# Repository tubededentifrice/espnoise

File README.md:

# ESPNoise

ESPNoise is a privacy-first noise warning sign for shared workspaces. An ESP32
measures sound energy and lights the word **NOISE** only when the room stays
loud. Short sounds, such as a cough or a dropped object, do not start the
alarm by themselves.

The repository includes the production enclosure, hardware design, PlatformIO
firmware, and an optional iPhone settings app.

## Main features

- Sustained-noise detection with a rolling decision window
- Green, orange, and red warning levels
- Ten SK6812 RGB plus warm-white pixels behind a printed diffuser
- Optional passive buzzer with a hard power switch
- A 30-minute mute button
- No raw microphone recording or storage
- Wi-Fi off; Bluetooth Low Energy is used only for the optional app
- Firmware targets for a full-size ESP32 and a LOLIN32 Lite

## Production build

The production build uses a full-size ESP32 board and a separate, power-only
USB-C input. A regulated 5 V supply powers the controller and peripherals. The
ESP32 USB-C port stays inside the enclosure as a firmware-service port. No
battery is necessary.

| Item | Production specification |
| --- | --- |
| Controller | Full-size ESP32 development board with USB-C |
| Microphone | ICS-43434 digital I2S microphone on the carrier PCB |
| Display | 10 SK6812 RGB plus warm-white, 32-bit pixels |
| Data buffer | SN74AHCT125PWR, 3.3 V input to 5 V output |
| Sound | 5 V passive electromagnetic buzzer and MMBT3904 driver |
| Controls | Momentary mute button and maintained hard buzzer switch |
| Power | Regulated 5 V, 2 A minimum; 3 A recommended |
| Enclosure | 164 mm × 54 mm × 54.5 mm main case envelope |

See the [bill of materials](docs/bom.md) for the complete part specification.

## 3D-print files

The ready-to-print package and editable source are in
[`cad/production`](cad/production). Start with one of these files:

- [`espnoise.3mf`](cad/production/espnoise.3mf) contains four arranged plates
  and the saved Bambu Studio print profile.
- [`espnoise.f3d`](cad/production/espnoise.f3d) is the editable Autodesk Fusion
  design.
- The individual STL files support other slicers and printers.

The package contains the case, back, reflector, illuminated letters, optional
letter mould, mute-button cap, and buzzer-switch cap.

| Reflector and switch cap | Case, back, and button cap | Letters | Letter mould |
| :---: | :---: | :---: | :---: |
|  |  |  |  |

The saved profile uses a 0.4 mm nozzle, 0.2 mm layers, two wall loops, 15%
infill, and no supports. Check the profile for your printer and material before
you print. See the [enclosure guide](cad/README.md) for file dimensions,
materials, and assembly notes.

## Wiring

The production wiring uses one common ground. The LED supply does not pass
through the ESP32 board.

```mermaid
flowchart LR
  USB["External power-only USB-C<br>5 V"] --> SPLIT["5 V and GND split"]
  SPLIT --> ESP["ESP32<br>5V/VIN and GND"]
  SPLIT --> FUSE["0.5 A hold fuse"]
  FUSE --> RAIL["5 V peripheral rail"]

  ESP -->|"3V3, GND<br>GPIO26 SCK<br>GPIO25 WS<br>GPIO32 SD"| MIC["ICS-43434<br>L/R to GND"]
  ESP -->|"GPIO18"| AHCT["SN74AHCT125PWR<br>5 V supply"]
  AHCT -->|"330 ohm"| LED["10 × SK6812 RGBW<br>5 V at both ends"]
  RAIL --> AHCT
  RAIL --> LED

  ESP -->|"GPIO23 PWM<br>through 1 kohm"| Q1["MMBT3904 driver"]
  RAIL --> SW["Hard buzzer<br>power switch"]
  SW --> BUZ["Passive magnetic buzzer"]
  BUZ --> Q1

  BTN["Mute button<br>GPIO27 to GND"] --> ESP
```

| Function | ESP32 pin |
| --- | ---: |
| ICS-43434 clock | GPIO26 |
| ICS-43434 word select | GPIO25 |
| ICS-43434 data | GPIO32 |
| SK6812 data through SN74AHCT125PWR | GPIO18 |
| Buzzer PWM through 1 kohm and MMBT3904 | GPIO23 |
| Mute button to GND | GPIO27 |
| Optional battery-boost enable | GPIO13 |

Keep the buzzer switch in the buzzer 5 V wire. Software must not override this
switch. Keep the external two-wire USB-C input separate from the ESP32
firmware-service port. If the power input exposes CC1 and CC2, connect one
5.1 kohm pull-down from each CC pin to GND. Do not connect CC1 to CC2.

See the [complete wiring guide](docs/wiring.md) and the
[interactive prototype-board diagram](docs/prototype-board-wiring.html) before
assembly.

## How detection works

The default rule listens for one second in each ten-second period. It stores
only the maximum sound level from each observation. At least three of the last
six observations must cross a threshold before the alarm starts. Two quiet
checks clear an active alarm.

The default thresholds are in dBFS until you calibrate the unit against a sound
level meter. They are not certified dBA values. Detector values and thresholds
are in [`firmware/include/config.h`](firmware/include/config.h).

## Build guide

1. Check the [bill of materials](docs/bom.md).
2. Print and prepare the [production enclosure](cad/README.md).
3. Follow the [modular assembly stages](docs/modular-build.md).
4. Make the connections in the [wiring guide](docs/wiring.md).
5. Build and upload the [firmware](firmware/README.md).
6. Use the [test and adjustment procedure](docs/detection.md).
7. If necessary, install and configure the optional iPhone app as described in
   [the app and Bluetooth guide](docs/app-and-bluetooth.md).

## Safety and privacy

- Start a new or changed build at 25% LED brightness or less. The production
  USB profile uses its higher limit only after the documented power test.
- Disconnect external 5 V power before you connect the ESP32 service USB port.
- Do not connect a battery to the full-size ESP32 board.
- For the optional battery build, use one protected 3.7 V LiPo pack with the
  correct plug polarity. Do not use loose lithium cells.
- Do not cover the microphone acoustic hole.
- The firmware processes sound levels in memory and does not save raw audio.

## Repository map

```text
cad/                 Production 3D-print files and editable CAD source
docs/                Hardware, wiring, assembly, and test guides
firmware/            PlatformIO firmware for both ESP32 controller options
ios/                 Optional iPhone companion app and Xcode project
```

## License

This project uses the [Functional Source License 1.1, ALv2 Future
License](LICENSE.md). Each release changes to the Apache License 2.0 two years
after that release first becomes available.

FSL is a source-available license before the change date. It permits study,
modification, redistribution, and most uses, but it limits competing commercial
products and services until the change date.

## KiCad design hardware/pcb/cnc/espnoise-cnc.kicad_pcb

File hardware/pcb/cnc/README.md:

# ESPNoise Rev C CNC unit

This directory contains a two-copper-face PCB for the Genmitsu Cubiko. One
nominal 70 mm by 50 mm FR-4 blank can make two units. The machine files contain
one unit only. Run each unit file, rotate the complete blank by 180 degrees in
its plane, set the work origin again, and run the same file a second time.

This method references each unit from an outside factory edge. An error in the
blank height stays in the center area. The file does not contain a second,
rotated unit. The rear-copper file still contains the X mirror that is required
for a left-to-right copper-face flip.

The mute button, hard buzzer switch, microphone acoustic center, and buzzer
center are on one line at local Y = 12.25 mm. Their local X positions are
6.5 mm, 17.5 mm, 35.5 mm, and 60.5 mm. All other component bodies and all wire
terminals are on the internal face.

The electrical schematic is in `espnoise-cnc-schematic.svg`. The exact pin
connections are in `pinout.md` and `espnoise-cnc-netlist.csv`. The editable
unit PCB is `espnoise-cnc.kicad_pcb`. The generator is the controlled layout
source.

This layout uses the measured buzzer dimensions, the confirmed microphone pin
pattern, and a centered microphone acoustic hole. The microphone body diameter
is approximately 13 mm. Print `espnoise-component-fit-check.svg` at 100% scale
and put the real parts on the drawing before you mill the complete blank.

## Important design limits

- Nominal raw blank: 70 mm by 50 mm
- Unit job area: 70 mm by 24.5 mm
- Supported assumed minimum blank: 69 mm by 49 mm
- Layout shift: 0.50 mm toward the left edge
- Copper faces: two
- Minimum track width: 1.00 mm
- Minimum checked copper clearance: 0.40 mm
- Power track width: 1.30 mm
- Milled isolation width: 0.40 mm
- Microphone pads: 2.00 mm copper with 1.00 mm holes
- Buzzer pads: 2.00 mm copper with 0.80 mm holes
- Mounting hole: one 2.0 mm hole at X = 34.5 mm for each unit run
- Wire vias: 0.8 mm holes with 1.7 mm copper pads
- No plated holes and no solder mask
- 1.2 mm holes for the individual wire terminals
- No insulated link wires
- No LED logic-level IC

The board uses direct insulated wires instead of cable headers. The exact
signal for each pad is in `pinout.md`, the netlist, the schematic, and the
internal-face SVG.

| Pad group | Connection |
| --- | --- |
| PWR1-1 / PWR1-2 | External +5 V / GND |
| J_ESP32-1 through J_ESP32-9 | ESP32 5 V, GND, 3.3 V, and six GPIO wires |
| J_LED-1 / J_LED-2 / J_LED-3 | LED +5 V / DIN / GND |

The LED data path is a direct trace from ESP32 GPIO18 to J_LED-2. This matches
the tested prototype. It is not a guaranteed 5 V logic interface. Keep the
wire short. If the installed strip is not reliable, add an external 5 V logic
buffer near the strip.

The buzzer driver parts stay on the board. The specified magnetic 5 V buzzer
must not connect directly to an ESP32 GPIO. SW2 stays as a hard switch in the
buzzer power wire and can remove all buzzer power.

MIC1 is the round MH-ET LIVE INMP441 module with two rows of three pins. With
the printed-label and acoustic-hole face toward the case top, and with the
notch at the local top edge, the top row is `GND`, `VDD`, `SD`. The bottom row
is `L/R`, `WS`, `SCK`. `L/R` connects to GND. This is the same view as the
supplied product image.

BZ1 is a 12 mm passive two-pin through-hole buzzer. Its lead pitch is 6.5 mm,
and each lead is 0.5 mm. Pad 1 is positive. Pad 2 is negative and connects to
the transistor collector.

## Generate the files

Install `pcb2gcode`. On macOS, use this command:

```sh
brew install pcb2gcode
```

Then run this command from the repository root:

```sh
uv run --locked opendle-cnc build --config opendle-tools.toml
```

The script does these tasks:

1. It generates one unit PCB.
2. It checks the board limits, body overlap, copper width, and clearance.
3. It makes one user-face isolation job and one mirrored internal-face job.
4. It makes one unit G-code file for each drill size.
5. It checks all X, Y, and Z limits and writes SHA-256 checksums.

The ready files are in `machine`. Do not run them until the coupon and the
preflight checks in `cubiko-guide.md` pass.

## Source files

| File | Purpose |
| --- | --- |
| `generate_cnc_board.py` | Unit source, router, and checks |
| `espnoise-cnc.kicad_pcb` | Editable and reviewable 70 mm by 24.5 mm unit |
| `espnoise-cnc-user.svg` | Single-unit user-face check view |
| `espnoise-cnc-internal.svg` | Single-unit internal-face check view |
| `espnoise-cnc-schematic.svg` | Electrical schematic |
| `pinout.md` | Complete pad and connector pin map |
| `espnoise-component-fit-check.svg` | 1:1 physical part fit check |
| `espnoise-cnc-netlist.csv` | Exact pin-to-net table |
| `espnoise-cnc-bom.csv` | Parts and face assignment for one unit |
| `millproject` | Single-unit isolation values |
| `millproject-coupon` | Coupon isolation values |
| `opendle-tools.toml` | Project paths, process values, and machine limits |
| `opendle-electronics` | Pinned shared CAM, G-code checks, and manifests |

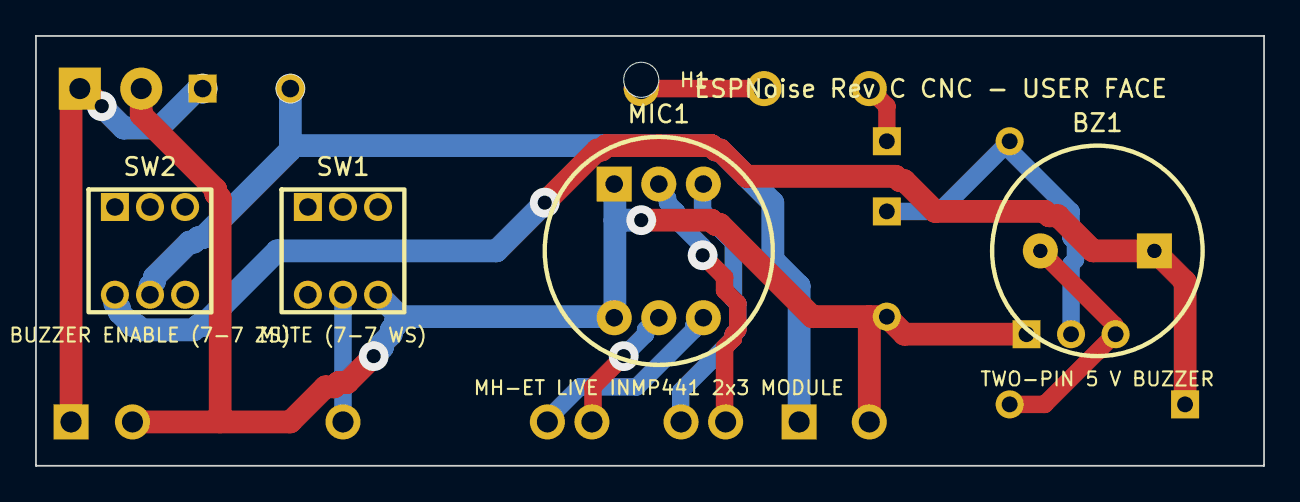
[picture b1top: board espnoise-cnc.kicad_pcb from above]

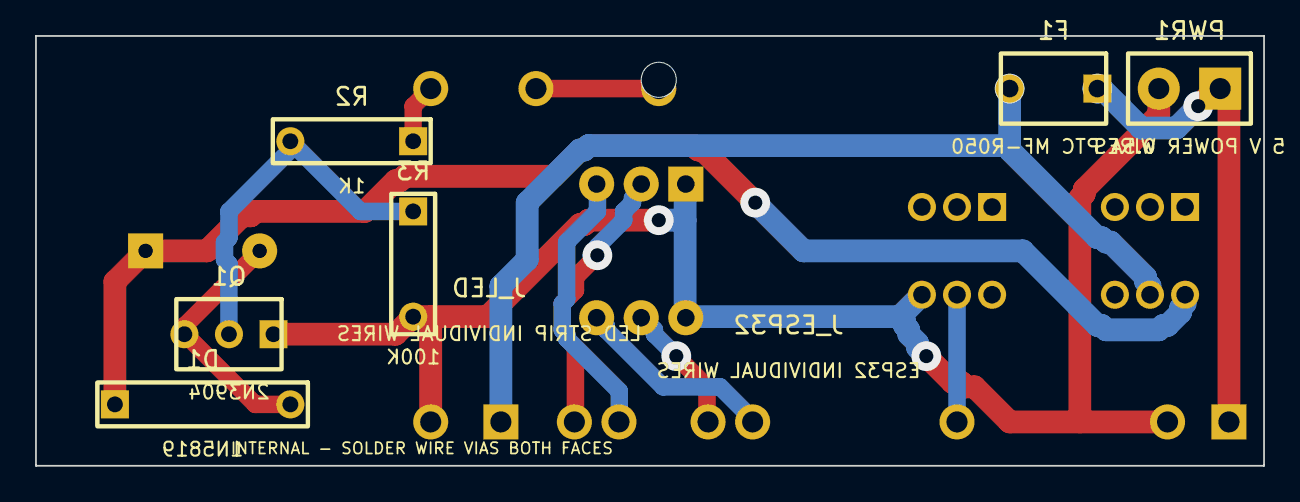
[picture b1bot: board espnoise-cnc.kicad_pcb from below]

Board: 2 copper layers, 70.0 x 24.5 mm, 13 parts (8 on the bottom side), 13 nets.

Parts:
BZ1: TWO-PIN 5 V BUZZER; Buzzer_THT_2Pin_P6.50mm_D12mm
D1: 1N5819; Axial
F1: 0.5A PTC MF-R050; Fuse_Radial_P5.00mm
H1: RegistrationHole_2mm
J_ESP32: ESP32 INDIVIDUAL WIRES; IndividualWireGroup_ESP32
J_LED: LED STRIP INDIVIDUAL WIRES; IndividualWireGroup_LED
MIC1: MH-ET LIVE INMP441 2x3 MODULE; MH_ET_LIVE_INMP441_2x3_P2.54_Row7.62
PWR1: 5 V POWER WIRES; WirePads_2_P3.5mm
Q1: 2N3904; TO-92_Inline_EBC
R2: 1K; Axial
R3: 100K; Axial
SW1: MUTE (7-7 WS); 7x7_DPDT_Pushbutton
SW2: BUZZER ENABLE (7-7 ZS); 7x7_DPDT_Pushbutton

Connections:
+3V3: J_ESP32.3, MIC1.2
+5V_BUZZER_SW: BZ1.1, D1.1, SW2.4
+5V_IN: F1.1, J_ESP32.1, PWR1.1
+5V_PERIPH: F1.2, J_LED.1, SW2.5
BUZZER_BASE: Q1.2, R2.2, R3.1
BUZZER_COLLECTOR: BZ1.2, D1.2, Q1.3
BUZZER_PWM: J_ESP32.8, R2.1
GND: J_ESP32.2, J_LED.3, MIC1.1, MIC1.4, PWR1.2, Q1.1, R3.2, SW1.6
LED_DATA: J_ESP32.7, J_LED.2
MIC_SCK: J_ESP32.4, MIC1.6
MIC_SD: J_ESP32.6, MIC1.3
MIC_WS: J_ESP32.5, MIC1.5
MUTE_N: J_ESP32.9, SW1.5

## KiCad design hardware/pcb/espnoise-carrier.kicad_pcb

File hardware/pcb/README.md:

# ESPNoise carrier PCB

For the nominal 70 mm by 50 mm home-milled blank, use
[`cnc/README.md`](cnc/README.md). The Cubiko files contain one unit. Run them
twice with a 180-degree blank rotation between the two runs. The prototype uses
larger through-hole parts, individual wire terminals, registration holes,
Gerber files, and Cubiko G-code.
The Rev B factory board below stays separate.

This directory contains the carrier PCB for the USB-powered ESPNoise build.
The ESP32 stays on a removable cable. The PCB contains the controls, digital
microphone, buzzer, LED data buffer, buzzer driver, fuse, and keyed connectors.

The board is 80 mm by 20 mm. Its nominal stack is two copper layers, 1.6 mm
FR-4, 1 oz copper, lead-free HASL, and a green solder mask.

## Interface summary

The controller, LED, and USB-C power connectors are JST PH vertical headers on
the lower face. A cable enters each connector in the direction away from that
face. The two switches, microphone opening, and buzzer are on the 10 mm board
centerline and face the case top.

MIC1 is on the lower face because it is a bottom-port microphone. A 0.5 mm
non-plated hole carries sound from the case top to the microphone port. Do not
cover this hole with glue, foam, or a label.

The controller interface uses signal names. It does not depend on the physical
size of the ESP32 board. Make one adapter cable for the selected controller.
The current `esp32dev` pin map is in `docs/wiring.md`. An ESP32-C3 needs a
separate firmware target and a different adapter cable before use.

## Factory order files

The `jlcpcb` directory contains these order files:

- `espnoise-carrier-gerbers.zip`: PCB fabrication data.
- `espnoise-carrier-bom.csv`: component list for assembly.
- `espnoise-carrier-cpl.csv`: component placement data.
- `espnoise-carrier-top.svg` and `espnoise-carrier-bottom.svg`: assembly views.

Upload the Gerber ZIP in the JLCPCB PCB order page. Enable PCB assembly, and
then upload the BOM and CPL files. Check every mapped part and orientation in
the assembly preview. In particular, check C2 and D1 polarity, MIC1 pin 1, pin
1 of all JST connectors, BZ1 polarity, and the six pins on each switch.

JLCPCB stock can change. Do not submit the order if the site replaces a part
without a new electrical and footprint check.

## Regeneration

Run `uv run --locked opendle-kicad export --config opendle-tools.toml` from the
repository root. The pinned shared tool needs KiCad 10 and its Python `pcbnew`
module. It regenerates the board, Gerbers, drill files, BOM, CPL, assembly
views, and hash manifest.

The generator is the controlled source for the board layout. Do not edit the
generated board without the same change in `generate_board.py`.

Use these documents with the order package:

- `electrical-design.md` gives the circuit and selected factory parts.
- `controller-adapters.md` gives all cable pin orders.
- `order-guide.md` gives the JLCPCB upload and preview checks.

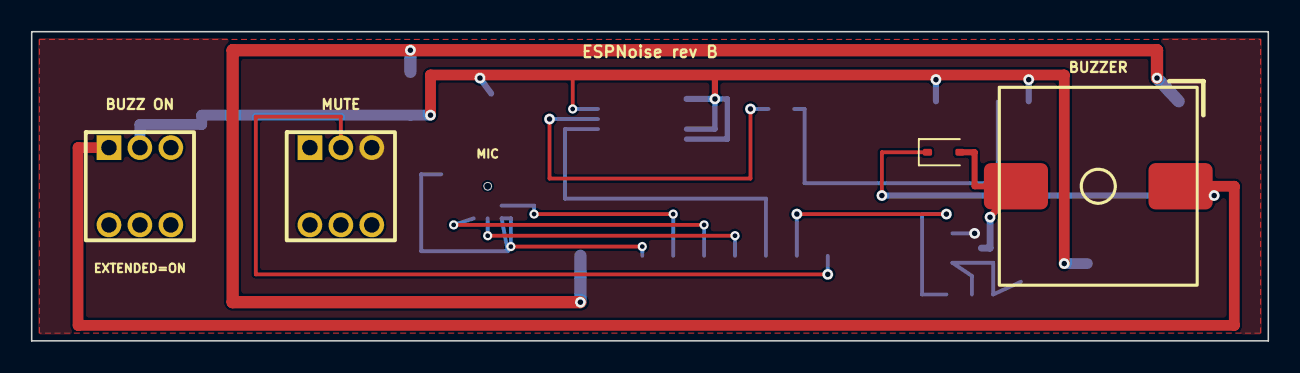
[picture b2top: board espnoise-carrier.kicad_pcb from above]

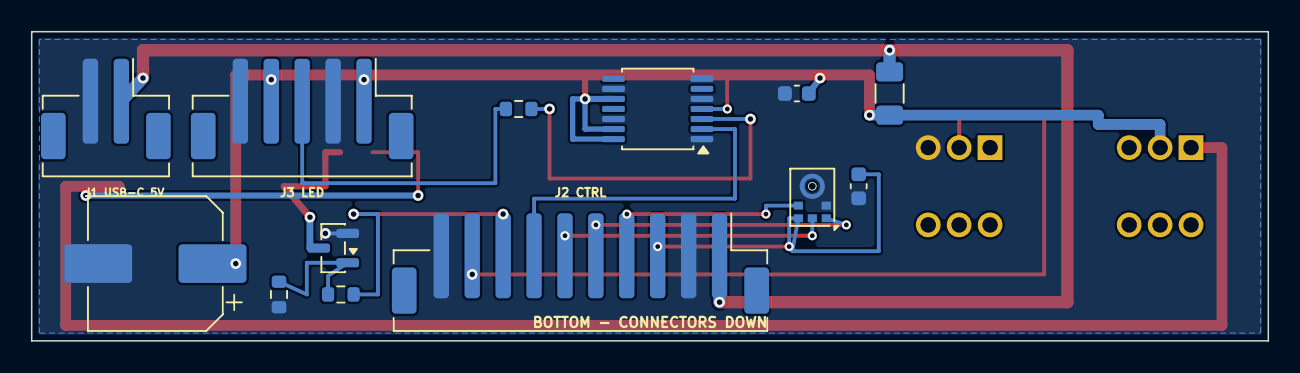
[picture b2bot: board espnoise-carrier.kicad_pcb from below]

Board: 2 copper layers, 80.0 x 20.0 mm, 17 parts (13 on the bottom side), 15 nets.

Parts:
BZ1: FUET-1370F-05; ESPNoise_FUET-1370F-05
C1, C3: 100nF; C_0603_1608Metric
C2: 1000uF 10V; CP_Elec_8x10.5
D1: 1N5819WS; D_SOD-323
F1: 0.5A PTC; Fuse_1206_3216Metric
J1: USB-C 5V; JST_PH_B2B-PH-SM4-TB_1x02-1MP_P2.00mm_Vertical
J2: CONTROLLER; JST_PH_B10B-PH-SM4-TB_1x10-1MP_P2.00mm_Vertical
J3: LED STRIP; JST_PH_B5B-PH-SM4-TB_1x05-1MP_P2.00mm_Vertical
MIC1: ICS-43434; InvenSense_ICS-43434-6_3.5x2.65mm
Q1: MMBT3904; SOT-23
R1: 330R; R_0603_1608Metric
R2: 1k; R_0603_1608Metric
R3: 100k; R_0603_1608Metric
SW1: MUTE; ESPNoise_7x7_DPDT_Pushbutton
SW2: BUZZER ENABLE; ESPNoise_7x7_DPDT_Pushbutton
U1: SN74AHCT125PWR; TSSOP-14_4.4x5mm_P0.65mm

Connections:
+3V3: C3.1, J2.3, MIC1.5
+5V_BUZZER_SW: BZ1.1, D1.1, SW2.1
+5V_IN: F1.1, J1.1, J2.1
+5V_PERIPH: C1.1, C2.1, F1.2, J3.1, J3.4, SW2.2, U1.4, U1.10, U1.13, U1.14
BUZZER_BASE: Q1.1, R2.2, R3.1
BUZZER_COLLECTOR: BZ1.2, D1.2, Q1.3
BUZZER_PWM: J2.8, R2.1
GND: C1.2, C2.2, C3.2, J1.2, J2.2, J2.10, J3.2, J3.5, MIC1.2, MIC1.3, Q1.2, R3.2, SW1.3, U1.1, U1.5, U1.7, U1.9, U1.12
LED_DATA_3V3: J2.7, U1.2
LED_DATA_5V: J3.3, R1.2
LED_DATA_5V_RAW: R1.1, U1.3
MIC_SCK: J2.4, MIC1.4
MIC_SD: J2.6, MIC1.6
MIC_WS: J2.5, MIC1.1
MUTE_N: J2.9, SW1.2

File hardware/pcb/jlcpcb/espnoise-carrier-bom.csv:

Comment,Designator,Footprint,LCSC Part #
0.5A PTC,F1,Fuse_1206_3216Metric,C163512
1000uF 10V,C2,CP_Elec_8x10.5,C5246577
100k,R3,R_0603_1608Metric,C25803
100nF,"C1,C3",C_0603_1608Metric,C14663
1N5819WS,D1,D_SOD-323,C191023
1k,R2,R_0603_1608Metric,C21190
330R,R1,R_0603_1608Metric,C23138
BUZZER ENABLE,SW2,ESPNoise_7x7_DPDT_Pushbutton,C5379891
CONTROLLER,J2,JST_PH_B10B-PH-SM4-TB_1x10-1MP_P2.00mm_Vertical,C265112
FUET-1370F-05,BZ1,ESPNoise_FUET-1370F-05,C2690507
ICS-43434,MIC1,InvenSense_ICS-43434-6_3.5x2.65mm,C5656610
LED STRIP,J3,JST_PH_B5B-PH-SM4-TB_1x05-1MP_P2.00mm_Vertical,C265086
MMBT3904,Q1,SOT-23,C181119
MUTE,SW1,ESPNoise_7x7_DPDT_Pushbutton,C5379890
SN74AHCT125PWR,U1,TSSOP-14_4.4x5mm_P0.65mm,C36365
USB-C 5V,J1,JST_PH_B2B-PH-SM4-TB_1x02-1MP_P2.00mm_Vertical,C265003

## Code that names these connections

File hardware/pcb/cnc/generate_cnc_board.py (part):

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            terminal(8, 48.0, 3.0, "BUZZER_PWM"),
            terminal(9, 18.0, 22.0, "MUTE_N"),
        ),
        "Pins: 1 VIN/5V, 2 GND, 3 3V3, 4 GPIO26 MIC_SCK, 5 GPIO25 MIC_WS, 6 GPIO32 MIC_SD, 7 GPIO18 LED_DATA, 8 GPIO23 BUZZER_PWM, 9 GPIO27 MUTE_N.",
        "ESPNoise:IndividualWireGroup_ESP32",
        "none",
    )
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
